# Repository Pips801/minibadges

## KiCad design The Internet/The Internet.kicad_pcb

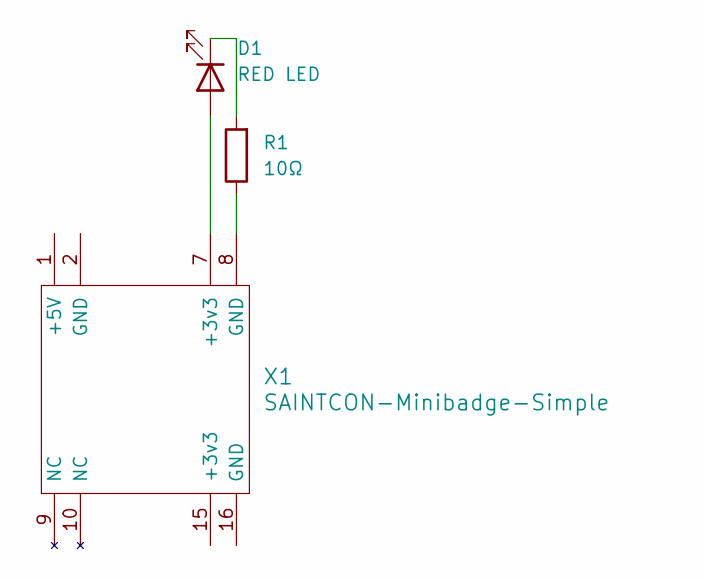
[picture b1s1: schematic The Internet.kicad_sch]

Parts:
D1: RED LED; LED_D3.0mm_FlatTop
R1: 10Ω; R_Box_L8.4mm_W2.5mm_P5.08mm
X1: SAINTCON-Minibadge-Simple

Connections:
unnamed: D1.2 (A), X1.7 (+3v3)
unnamed: D1.1 (K), R1.2
unnamed: R1.1, X1.8 (GND)

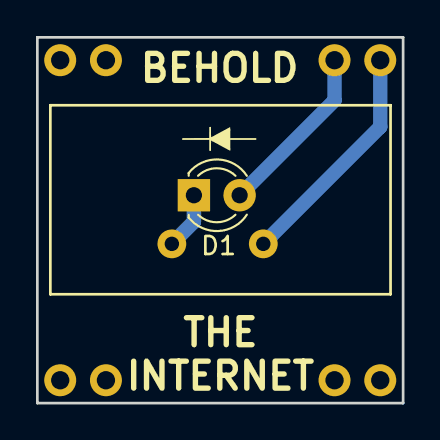
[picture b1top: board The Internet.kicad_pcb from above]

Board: 2 copper layers, 20.3 x 20.3 mm, 3 parts (1 on the bottom side), 3 nets.

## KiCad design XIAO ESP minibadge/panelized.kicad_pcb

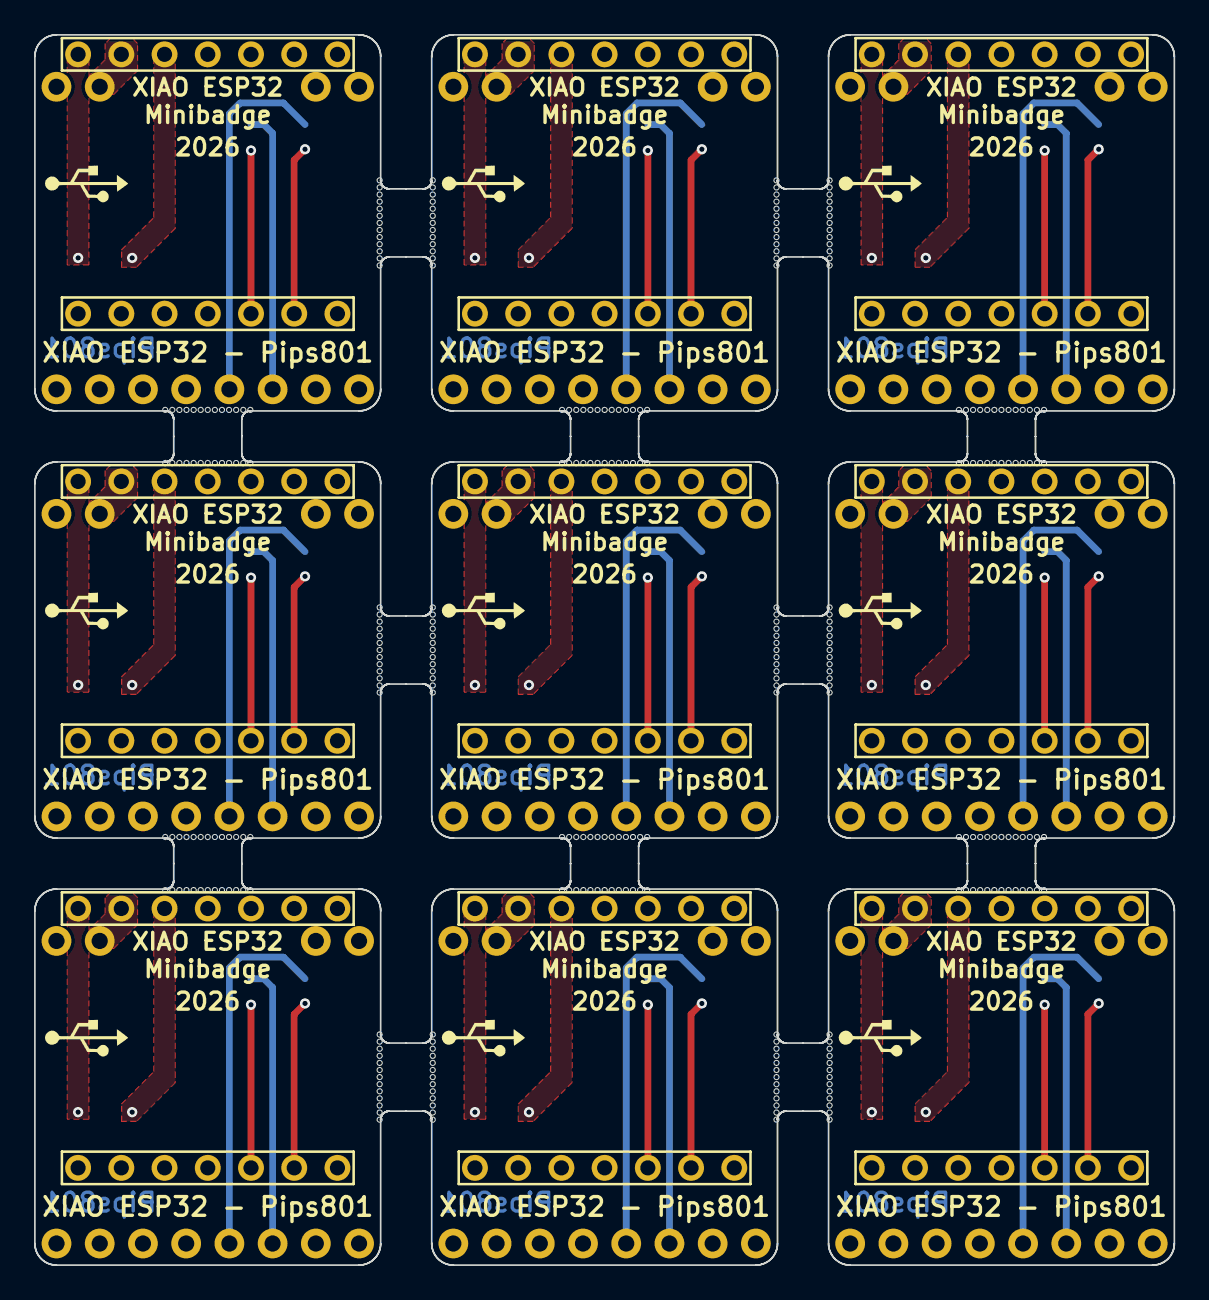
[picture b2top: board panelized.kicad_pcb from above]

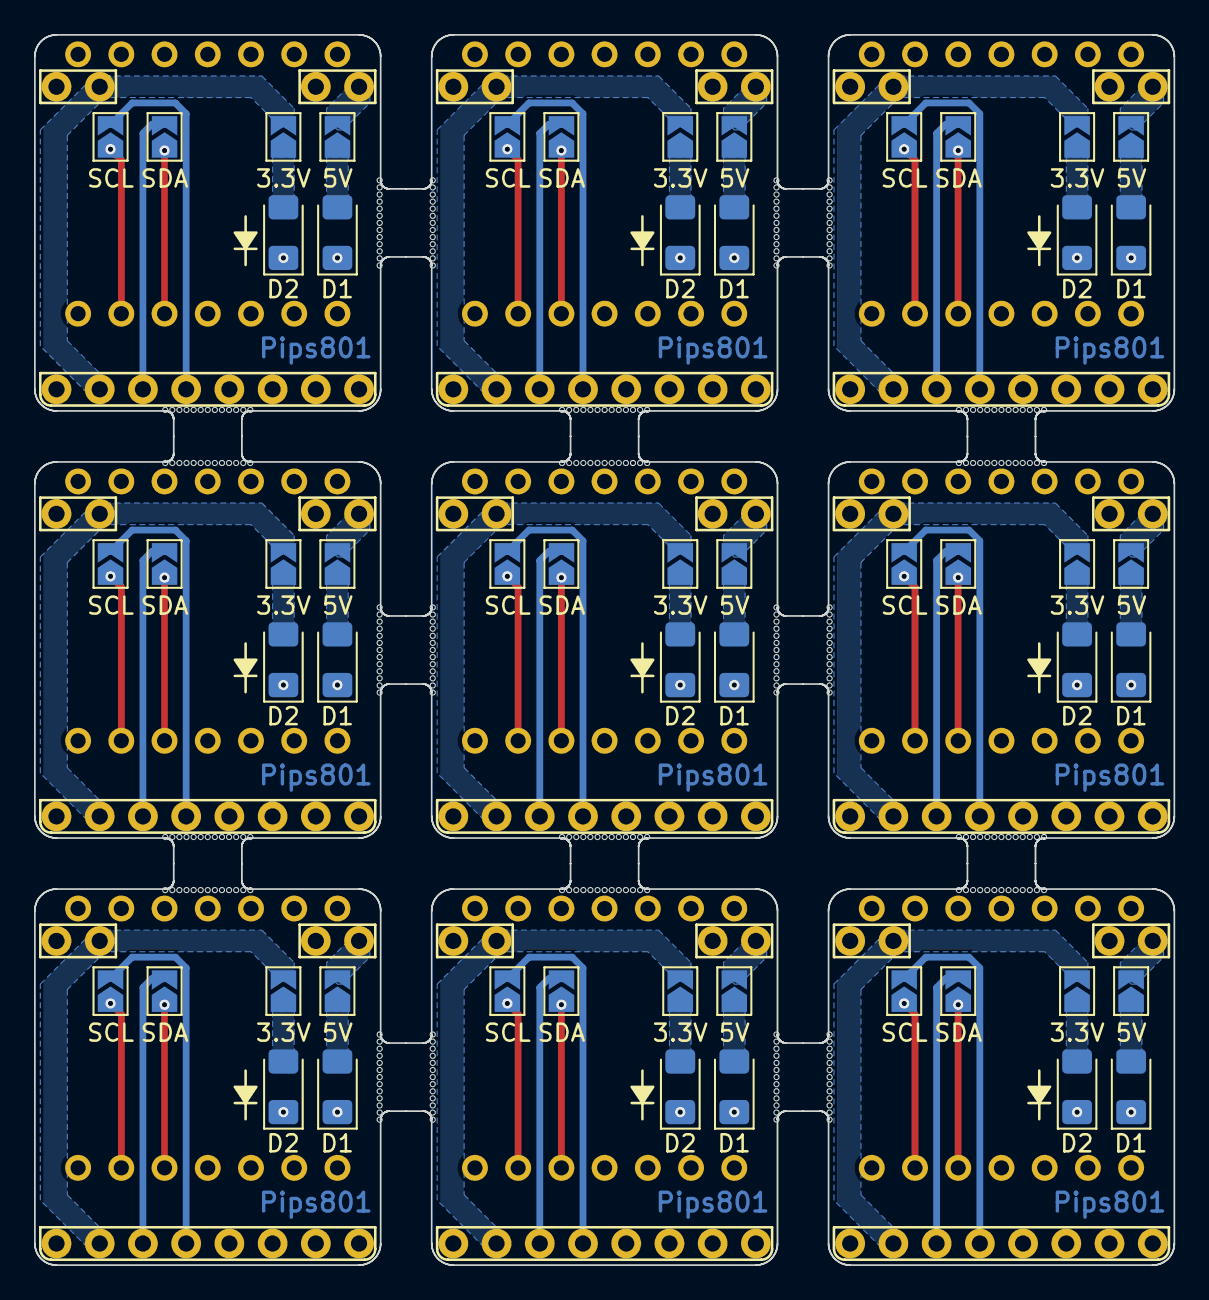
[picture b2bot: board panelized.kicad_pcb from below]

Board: 2 copper layers, 67.0 x 72.3 mm, 384 parts (54 on the bottom side), 99 nets.

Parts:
D1, D1#2, D1#3, D1#4, D1#5, D1#6, D1#7, D1#8, D1#9, D2, D2#2, D2#3, D2#4, D2#5, D2#6, D2#7, D2#8, D2#9: 10V; D_1206_3216Metric_Pad1.42x1.75mm_HandSolder
JP1, JP1#2, JP1#3, JP1#4, JP1#5, JP1#6, JP1#7, JP1#8, JP1#9: 5V; SolderJumper-2_P1.3mm_Open_TrianglePad1.0x1.5mm
JP2, JP2#2, JP2#3, JP2#4, JP2#5, JP2#6, JP2#7, JP2#8, JP2#9: 3.3V; SolderJumper-2_P1.3mm_Open_TrianglePad1.0x1.5mm
JP3, JP3#2, JP3#3, JP3#4, JP3#5, JP3#6, JP3#7, JP3#8, JP3#9: SCL; SolderJumper-2_P1.3mm_Open_TrianglePad1.0x1.5mm
JP4, JP4#2, JP4#3, JP4#4, JP4#5, JP4#6, JP4#7, JP4#8, JP4#9: SDA; SolderJumper-2_P1.3mm_Open_TrianglePad1.0x1.5mm
KiKit_MB_1_1, KiKit_MB_1_2, KiKit_MB_1_3, KiKit_MB_1_4, KiKit_MB_1_5, KiKit_MB_1_6, KiKit_MB_1_7, KiKit_MB_1_8, KiKit_MB_1_9, KiKit_MB_1_10, KiKit_MB_1_11, KiKit_MB_1_12, KiKit_MB_1_13, KiKit_MB_2_1, KiKit_MB_2_2, KiKit_MB_2_3, KiKit_MB_2_4, KiKit_MB_2_5, KiKit_MB_2_6, KiKit_MB_2_7, KiKit_MB_2_8, KiKit_MB_2_9, KiKit_MB_2_10, KiKit_MB_2_11, KiKit_MB_2_12, KiKit_MB_2_13, KiKit_MB_3_1, KiKit_MB_3_2, KiKit_MB_3_3, KiKit_MB_3_4, KiKit_MB_3_5, KiKit_MB_3_6, KiKit_MB_3_7, KiKit_MB_3_8, KiKit_MB_3_9, KiKit_MB_3_10, KiKit_MB_3_11, KiKit_MB_3_12, KiKit_MB_3_13, KiKit_MB_4_1, KiKit_MB_4_2, KiKit_MB_4_3, KiKit_MB_4_4, KiKit_MB_4_5, KiKit_MB_4_6, KiKit_MB_4_7, KiKit_MB_4_8, KiKit_MB_4_9, KiKit_MB_4_10, KiKit_MB_4_11, KiKit_MB_4_12, KiKit_MB_4_13, KiKit_MB_5_1, KiKit_MB_5_2, KiKit_MB_5_3, KiKit_MB_5_4, KiKit_MB_5_5, KiKit_MB_5_6, KiKit_MB_5_7, KiKit_MB_5_8, KiKit_MB_5_9, KiKit_MB_5_10, KiKit_MB_5_11, KiKit_MB_5_12, KiKit_MB_5_13, KiKit_MB_6_1, KiKit_MB_6_2, KiKit_MB_6_3, KiKit_MB_6_4, KiKit_MB_6_5, KiKit_MB_6_6, KiKit_MB_6_7, KiKit_MB_6_8, KiKit_MB_6_9, KiKit_MB_6_10, KiKit_MB_6_11, KiKit_MB_6_12, KiKit_MB_6_13, KiKit_MB_7_1, KiKit_MB_7_2, KiKit_MB_7_3, KiKit_MB_7_4, KiKit_MB_7_5, KiKit_MB_7_6, KiKit_MB_7_7, KiKit_MB_7_8, KiKit_MB_7_9, KiKit_MB_7_10, KiKit_MB_7_11, KiKit_MB_7_12, KiKit_MB_7_13, KiKit_MB_8_1, KiKit_MB_8_2, KiKit_MB_8_3, KiKit_MB_8_4, KiKit_MB_8_5, KiKit_MB_8_6, KiKit_MB_8_7, KiKit_MB_8_8, KiKit_MB_8_9, KiKit_MB_8_10, KiKit_MB_8_11, KiKit_MB_8_12, KiKit_MB_8_13, KiKit_MB_9_1, KiKit_MB_9_2, KiKit_MB_9_3, KiKit_MB_9_4, KiKit_MB_9_5, KiKit_MB_9_6, KiKit_MB_9_7, KiKit_MB_9_8, KiKit_MB_9_9, KiKit_MB_9_10, KiKit_MB_9_11, KiKit_MB_9_12, KiKit_MB_9_13, KiKit_MB_10_1, KiKit_MB_10_2, KiKit_MB_10_3, KiKit_MB_10_4, KiKit_MB_10_5, KiKit_MB_10_6, KiKit_MB_10_7, KiKit_MB_10_8, KiKit_MB_10_9, KiKit_MB_10_10, KiKit_MB_10_11, KiKit_MB_10_12, KiKit_MB_10_13, KiKit_MB_11_1, KiKit_MB_11_2, KiKit_MB_11_3, KiKit_MB_11_4, KiKit_MB_11_5, KiKit_MB_11_6, KiKit_MB_11_7, KiKit_MB_11_8, KiKit_MB_11_9, KiKit_MB_11_10, KiKit_MB_11_11, KiKit_MB_11_12, KiKit_MB_11_13, KiKit_MB_12_1, KiKit_MB_12_2, KiKit_MB_12_3, KiKit_MB_12_4, KiKit_MB_12_5, KiKit_MB_12_6, KiKit_MB_12_7, KiKit_MB_12_8, KiKit_MB_12_9, KiKit_MB_12_10, KiKit_MB_12_11, KiKit_MB_12_12, KiKit_MB_12_13, KiKit_MB_13_1, KiKit_MB_13_2, KiKit_MB_13_3, KiKit_MB_13_4, KiKit_MB_13_5, KiKit_MB_13_6, KiKit_MB_13_7, KiKit_MB_13_8, KiKit_MB_13_9, KiKit_MB_13_10, KiKit_MB_13_11, KiKit_MB_13_12, KiKit_MB_13_13, KiKit_MB_14_1, KiKit_MB_14_2, KiKit_MB_14_3, KiKit_MB_14_4, KiKit_MB_14_5, KiKit_MB_14_6, KiKit_MB_14_7, KiKit_MB_14_8, KiKit_MB_14_9, KiKit_MB_14_10, KiKit_MB_14_11, KiKit_MB_14_12, KiKit_MB_14_13, KiKit_MB_15_1, KiKit_MB_15_2, KiKit_MB_15_3, KiKit_MB_15_4, KiKit_MB_15_5, KiKit_MB_15_6, KiKit_MB_15_7, KiKit_MB_15_8, KiKit_MB_15_9, KiKit_MB_15_10, KiKit_MB_15_11, KiKit_MB_15_12, KiKit_MB_15_13, KiKit_MB_16_1, KiKit_MB_16_2, KiKit_MB_16_3, KiKit_MB_16_4, KiKit_MB_16_5, KiKit_MB_16_6, KiKit_MB_16_7, KiKit_MB_16_8, KiKit_MB_16_9, KiKit_MB_16_10, KiKit_MB_16_11, KiKit_MB_16_12, KiKit_MB_16_13, KiKit_MB_17_1, KiKit_MB_17_2, KiKit_MB_17_3, KiKit_MB_17_4, KiKit_MB_17_5, KiKit_MB_17_6, KiKit_MB_17_7, KiKit_MB_17_8, KiKit_MB_17_9, KiKit_MB_17_10, KiKit_MB_17_11, KiKit_MB_17_12, KiKit_MB_17_13, KiKit_MB_18_1, KiKit_MB_18_2, KiKit_MB_18_3, KiKit_MB_18_4, KiKit_MB_18_5, KiKit_MB_18_6, KiKit_MB_18_7, KiKit_MB_18_8, KiKit_MB_18_9, KiKit_MB_18_10, KiKit_MB_18_11, KiKit_MB_18_12, KiKit_MB_18_13, KiKit_MB_19_1, KiKit_MB_19_2, KiKit_MB_19_3, KiKit_MB_19_4, KiKit_MB_19_5, KiKit_MB_19_6, KiKit_MB_19_7, KiKit_MB_19_8, KiKit_MB_19_9, KiKit_MB_19_10, KiKit_MB_19_11, KiKit_MB_19_12, KiKit_MB_19_13, KiKit_MB_20_1, KiKit_MB_20_2, KiKit_MB_20_3, KiKit_MB_20_4, KiKit_MB_20_5, KiKit_MB_20_6, KiKit_MB_20_7, KiKit_MB_20_8, KiKit_MB_20_9, KiKit_MB_20_10, KiKit_MB_20_11, KiKit_MB_20_12, KiKit_MB_20_13, KiKit_MB_21_1, KiKit_MB_21_2, KiKit_MB_21_3, KiKit_MB_21_4, KiKit_MB_21_5, KiKit_MB_21_6, KiKit_MB_21_7, KiKit_MB_21_8, KiKit_MB_21_9, KiKit_MB_21_10, KiKit_MB_21_11, KiKit_MB_21_12, KiKit_MB_21_13, KiKit_MB_22_1, KiKit_MB_22_2, KiKit_MB_22_3, KiKit_MB_22_4, KiKit_MB_22_5, KiKit_MB_22_6, KiKit_MB_22_7, KiKit_MB_22_8, KiKit_MB_22_9, KiKit_MB_22_10, KiKit_MB_22_11, KiKit_MB_22_12, KiKit_MB_22_13, KiKit_MB_23_1, KiKit_MB_23_2, KiKit_MB_23_3, KiKit_MB_23_4, KiKit_MB_23_5, KiKit_MB_23_6, KiKit_MB_23_7, KiKit_MB_23_8, KiKit_MB_23_9, KiKit_MB_23_10, KiKit_MB_23_11, KiKit_MB_23_12, KiKit_MB_23_13, KiKit_MB_24_1, KiKit_MB_24_2, KiKit_MB_24_3, KiKit_MB_24_4, KiKit_MB_24_5, KiKit_MB_24_6, KiKit_MB_24_7, KiKit_MB_24_8, KiKit_MB_24_9, KiKit_MB_24_10, KiKit_MB_24_11, KiKit_MB_24_12, KiKit_MB_24_13: NPTH
MB1, MB1#2, MB1#3, MB1#4, MB1#5, MB1#6, MB1#7, MB1#8, MB1#9: MiniBadge_Simple; MiniBadge_Full_NoEdges
U1, U1#2, U1#3, U1#4, U1#5, U1#6, U1#7, U1#8, U1#9: XIAO-ESP32-S3-DIP; XIAO-ESP32S3-DIP

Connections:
Board_0-+3.3V: JP2#2.2 (B), MB1#5.7 (+3V3), MB1#5.15 (3V3+)
Board_0-/X_3V3: D2#9.1 (K), U1#8.12 (VCC_3V3)
Board_0-/X_SCL: JP3.1 (A), U1#8.6 (GPIO9/D5/I2C_SCL)
Board_0-/X_SDA: JP4#6.1 (A), U1#8.5 (GPIO5/D4/I2C_SDA)
Board_0-/X_VBUS: D1#7.1 (K), U1#8.14 (VBUS)
Board_0-GND: MB1#5.2 (GND), MB1#5.8 (GND), MB1#5.16 (GND), U1#8.13 (GND)
Board_0-Net-(D1-A): D1#7.2 (A), JP1#9.1 (A)
Board_0-Net-(D2-A): D2#9.2 (A), JP2#2.1 (A)
Board_0-SCL: JP3.2 (B), MB1#5.13 (SCL)
Board_0-SDA: JP4#6.2 (B), MB1#5.14 (SDA)
Board_0-VBUS: JP1#9.2 (B), MB1#5.1 (+VBATT)
Board_1-+3.3V: JP2#9.2 (B), MB1#2.7 (+3V3), MB1#2.15 (3V3+)
Board_1-/X_3V3: D2#5.1 (K), U1.12 (VCC_3V3)
Board_1-/X_SCL: JP3#8.1 (A), U1.6 (GPIO9/D5/I2C_SCL)
Board_1-/X_SDA: JP4#2.1 (A), U1.5 (GPIO5/D4/I2C_SDA)
Board_1-/X_VBUS: D1#3.1 (K), U1.14 (VBUS)
Board_1-GND: MB1#2.2 (GND), MB1#2.8 (GND), MB1#2.16 (GND), U1.13 (GND)
Board_1-Net-(D1-A): D1#3.2 (A), JP1.1 (A)
Board_1-Net-(D2-A): D2#5.2 (A), JP2#9.1 (A)
Board_1-SCL: JP3#8.2 (B), MB1#2.13 (SCL)
Board_1-SDA: JP4#2.2 (B), MB1#2.14 (SDA)
Board_1-VBUS: JP1.2 (B), MB1#2.1 (+VBATT)
Board_2-+3.3V: JP2.2 (B), MB1#8.7 (+3V3), MB1#8.15 (3V3+)
Board_2-/X_3V3: D2#6.1 (K), U1#2.12 (VCC_3V3)
Board_2-/X_SCL: JP3#5.1 (A), U1#2.6 (GPIO9/D5/I2C_SCL)
Board_2-/X_SDA: JP4#9.1 (A), U1#2.5 (GPIO5/D4/I2C_SDA)
Board_2-/X_VBUS: D1.1 (K), U1#2.14 (VBUS)
Board_2-GND: MB1#8.2 (GND), MB1#8.8 (GND), MB1#8.16 (GND), U1#2.13 (GND)
Board_2-Net-(D1-A): D1.2 (A), JP1#7.1 (A)
Board_2-Net-(D2-A): D2#6.2 (A), JP2.1 (A)
Board_2-SCL: JP3#5.2 (B), MB1#8.13 (SCL)
Board_2-SDA: JP4#9.2 (B), MB1#8.14 (SDA)
Board_2-VBUS: JP1#7.2 (B), MB1#8.1 (+VBATT)
Board_3-+3.3V: JP2#5.2 (B), MB1#4.7 (+3V3), MB1#4.15 (3V3+)
Board_3-/X_3V3: D2#4.1 (K), U1#7.12 (VCC_3V3)
Board_3-/X_SCL: JP3#9.1 (A), U1#7.6 (GPIO9/D5/I2C_SCL)
Board_3-/X_SDA: JP4#5.1 (A), U1#7.5 (GPIO5/D4/I2C_SDA)
Board_3-/X_VBUS: D1#5.1 (K), U1#7.14 (VBUS)
Board_3-GND: MB1#4.2 (GND), MB1#4.8 (GND), MB1#4.16 (GND), U1#7.13 (GND)
Board_3-Net-(D1-A): D1#5.2 (A), JP1#4.1 (A)
Board_3-Net-(D2-A): D2#4.2 (A), JP2#5.1 (A)
Board_3-SCL: JP3#9.2 (B), MB1#4.13 (SCL)
Board_3-SDA: JP4#5.2 (B), MB1#4.14 (SDA)
Board_3-VBUS: JP1#4.2 (B), MB1#4.1 (+VBATT)
Board_4-+3.3V: JP2#7.2 (B), MB1#6.7 (+3V3), MB1#6.15 (3V3+)
Board_4-/X_3V3: D2#8.1 (K), U1#3.12 (VCC_3V3)
Board_4-/X_SCL: JP3#6.1 (A), U1#3.6 (GPIO9/D5/I2C_SCL)
Board_4-/X_SDA: JP4#8.1 (A), U1#3.5 (GPIO5/D4/I2C_SDA)
Board_4-/X_VBUS: D1#2.1 (K), U1#3.14 (VBUS)
Board_4-GND: MB1#6.2 (GND), MB1#6.8 (GND), MB1#6.16 (GND), U1#3.13 (GND)
Board_4-Net-(D1-A): D1#2.2 (A), JP1#6.1 (A)
Board_4-Net-(D2-A): D2#8.2 (A), JP2#7.1 (A)
Board_4-SCL: JP3#6.2 (B), MB1#6.13 (SCL)
Board_4-SDA: JP4#8.2 (B), MB1#6.14 (SDA)
Board_4-VBUS: JP1#6.2 (B), MB1#6.1 (+VBATT)
Board_5-+3.3V: JP2#4.2 (B), MB1#3.7 (+3V3), MB1#3.15 (3V3+)
Board_5-/X_3V3: D2#2.1 (K), U1#9.12 (VCC_3V3)
Board_5-/X_SCL: JP3#4.1 (A), U1#9.6 (GPIO9/D5/I2C_SCL)
Board_5-/X_SDA: JP4.1 (A), U1#9.5 (GPIO5/D4/I2C_SDA)
Board_5-/X_VBUS: D1#6.1 (K), U1#9.14 (VBUS)
Board_5-GND: MB1#3.2 (GND), MB1#3.8 (GND), MB1#3.16 (GND), U1#9.13 (GND)
Board_5-Net-(D1-A): D1#6.2 (A), JP1#3.1 (A)
Board_5-Net-(D2-A): D2#2.2 (A), JP2#4.1 (A)
Board_5-SCL: JP3#4.2 (B), MB1#3.13 (SCL)
Board_5-SDA: JP4.2 (B), MB1#3.14 (SDA)
Board_5-VBUS: JP1#3.2 (B), MB1#3.1 (+VBATT)
Board_6-+3.3V: JP2#8.2 (B), MB1#9.7 (+3V3), MB1#9.15 (3V3+)
Board_6-/X_3V3: D2#7.1 (K), U1#6.12 (VCC_3V3)
Board_6-/X_SCL: JP3#7.1 (A), U1#6.6 (GPIO9/D5/I2C_SCL)
Board_6-/X_SDA: JP4#7.1 (A), U1#6.5 (GPIO5/D4/I2C_SDA)
Board_6-/X_VBUS: D1#4.1 (K), U1#6.14 (VBUS)
Board_6-GND: MB1#9.2 (GND), MB1#9.8 (GND), MB1#9.16 (GND), U1#6.13 (GND)
Board_6-Net-(D1-A): D1#4.2 (A), JP1#5.1 (A)
Board_6-Net-(D2-A): D2#7.2 (A), JP2#8.1 (A)
Board_6-SCL: JP3#7.2 (B), MB1#9.13 (SCL)
Board_6-SDA: JP4#7.2 (B), MB1#9.14 (SDA)
Board_6-VBUS: JP1#5.2 (B), MB1#9.1 (+VBATT)
Board_7-+3.3V: JP2#6.2 (B), MB1.7 (+3V3), MB1.15 (3V3+)
Board_7-/X_3V3: D2#3.1 (K), U1#5.12 (VCC_3V3)
Board_7-/X_SCL: JP3#2.1 (A), U1#5.6 (GPIO9/D5/I2C_SCL)
Board_7-/X_SDA: JP4#3.1 (A), U1#5.5 (GPIO5/D4/I2C_SDA)
Board_7-/X_VBUS: D1#9.1 (K), U1#5.14 (VBUS)
Board_7-GND: MB1.2 (GND), MB1.8 (GND), MB1.16 (GND), U1#5.13 (GND)
Board_7-Net-(D1-A): D1#9.2 (A), JP1#2.1 (A)
Board_7-Net-(D2-A): D2#3.2 (A), JP2#6.1 (A)
Board_7-SCL: JP3#2.2 (B), MB1.13 (SCL)
Board_7-SDA: JP4#3.2 (B), MB1.14 (SDA)
Board_7-VBUS: JP1#2.2 (B), MB1.1 (+VBATT)
Board_8-+3.3V: JP2#3.2 (B), MB1#7.7 (+3V3), MB1#7.15 (3V3+)
Board_8-/X_3V3: D2.1 (K), U1#4.12 (VCC_3V3)
Board_8-/X_SCL: JP3#3.1 (A), U1#4.6 (GPIO9/D5/I2C_SCL)
Board_8-/X_SDA: JP4#4.1 (A), U1#4.5 (GPIO5/D4/I2C_SDA)
Board_8-/X_VBUS: D1#8.1 (K), U1#4.14 (VBUS)
Board_8-GND: MB1#7.2 (GND), MB1#7.8 (GND), MB1#7.16 (GND), U1#4.13 (GND)
Board_8-Net-(D1-A): D1#8.2 (A), JP1#8.1 (A)
Board_8-Net-(D2-A): D2.2 (A), JP2#3.1 (A)
Board_8-SCL: JP3#3.2 (B), MB1#7.13 (SCL)
Board_8-SDA: JP4#4.2 (B), MB1#7.14 (SDA)
Board_8-VBUS: JP1#8.2 (B), MB1#7.1 (+VBATT)
